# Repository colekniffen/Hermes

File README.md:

# Hermes

A small form factor, low power, RF module with a programmable STM32.  The goal of this project was to make a small board to mess around with RF and some basic DSP.

## Stack-up

I planned to manufacture this board through JLC PCB.  The service allows for cost-effective manufacturing with reasonable accuracy and constraints.  I decided to use an impedance-controlled, 4-layer stack-up because of the RF section (JLC04161H-7628).  This board is 1.6 mm thick with an outer copper weight of 1oz and inner copper weight of 0.5oz.  The stack-up information is important in determining the USB differential and RF antenna trace widths and/or spacing. 

## Design Considerations

### USB Connection
I decided to use a micro-USB connection for this board.  I chose this connector mainly for its size.  I did consider using USB-C since it's becoming more prevalent in modern electronics and similar in size.  However, USB-C has many connections which would not be useful in this case.  I did not need anything incredibly high-speed or with high power demand.  If one wanted to use USB-C with this board, it's possible to basically just swap out the connector and terminate it as per the USB-C specifications for USB-C to micro-USB.  If this is done, it may be wise to add current protection.  I left current protection out mainly to reduce the number of components, and the likelihood of micro-USB (due to the shape) having reverse current is incredibly low.  I did still include ESD protection though.

USB uses differential signals.  The specification for the USB protocol is to have 90 Ohm impedance traces.  To do this, I assumed a trace spacing of 8 mils.  The spacing could be reduced, but I chose this for ease of manufacturing.  Using the stack-up information and the differential spacing, trace widths are calculated to be 10.28 mil.

### Power
The USB connection to a host device will provide the board with 5V.  Most of the components on the board are designed for 3V3, so a voltage regulator is needed.  I chose the XC6206P332MR.  This is an efficient, low cost, and low noise LDO regulator. 

### Microcontroller
I chose to use the STM32L432KBU6 for this board.  It's low power and has a built in USB module.  This MCU doesn't have a ton of memory, but it will be used mainly for passing the RX/TX signal along to the host and do basic processing.  So, it has more than enough memory for its intended use.  Additionally, the core speed is more than enough to handle the transceiver's data.  

Assuming a 1ns rise time, which is faster than expected for this setup, the critical length is around 41.1 mm.  This means as long as the traces are less than 41.1 mm, impedance effects can largely be ignored for the MCU's digital signals (the board isn't even that long!).  Furthermore, assuming worst-case propagation delay, based on the PCB materials, of 180 ps/in, the slight differences in trace length won't make a huge difference.  The SPI traces are short and the fastest setup/hold times are around 1.5 ns, so the slight difference in SPI trace lengths (the skew in delay for the SPI signals is approximately 37.4 ps) will have virtually no effect on performance.  If the MCU was operating at GHz frequencies, problems would likely arise, but this length difference is okay for the fastest signals supported by this system. 

### Transceiver
I chose the nRF24L01+ which is a 2.4GHz transceiver (using [GFSK](https://en.wikipedia.org/wiki/Frequency-shift_keying#Gaussian_frequency-shift_keying) modulation).  This transceiver contains basically everything needed to perform the functions of most consumer electronics, so it is more than enough for experimenting with.  It has good documentation, a decent amount of customizability, and doesn't use a ton of power.  Additionally, The IC supports a variety of different antenna configurations, but I planned to connect a 2.4GHz passive, single-ended antenna.  Thus, I included the necessary matching and bias networks (assuming a 50 Ohm antenna) to meet the specifications as described by the data sheet.

To meet the impedance matching requirements, the antenna traces are to be 50 Ohms.  Using the stack-up information, the calculated trace width is 11.55mil.

## Datasheets
- [STM Datasheet](https://www.st.com/content/ccc/resource/technical/document/datasheet/24/01/9f/59/f0/83/47/fc/DM00257205.pdf/files/DM00257205.pdf/jcr:content/translations/en.DM00257205.pdf)
- [Transceiver Datasheet](https://www.sparkfun.com/datasheets/Components/SMD/nRF24L01Pluss_Preliminary_Product_Specification_v1_0.pdf)
- [ Linear and low-dropout regulator](https://www.mouser.com/datasheet/2/760/TOSL_S_A0007229533_1-2575067.pdf)

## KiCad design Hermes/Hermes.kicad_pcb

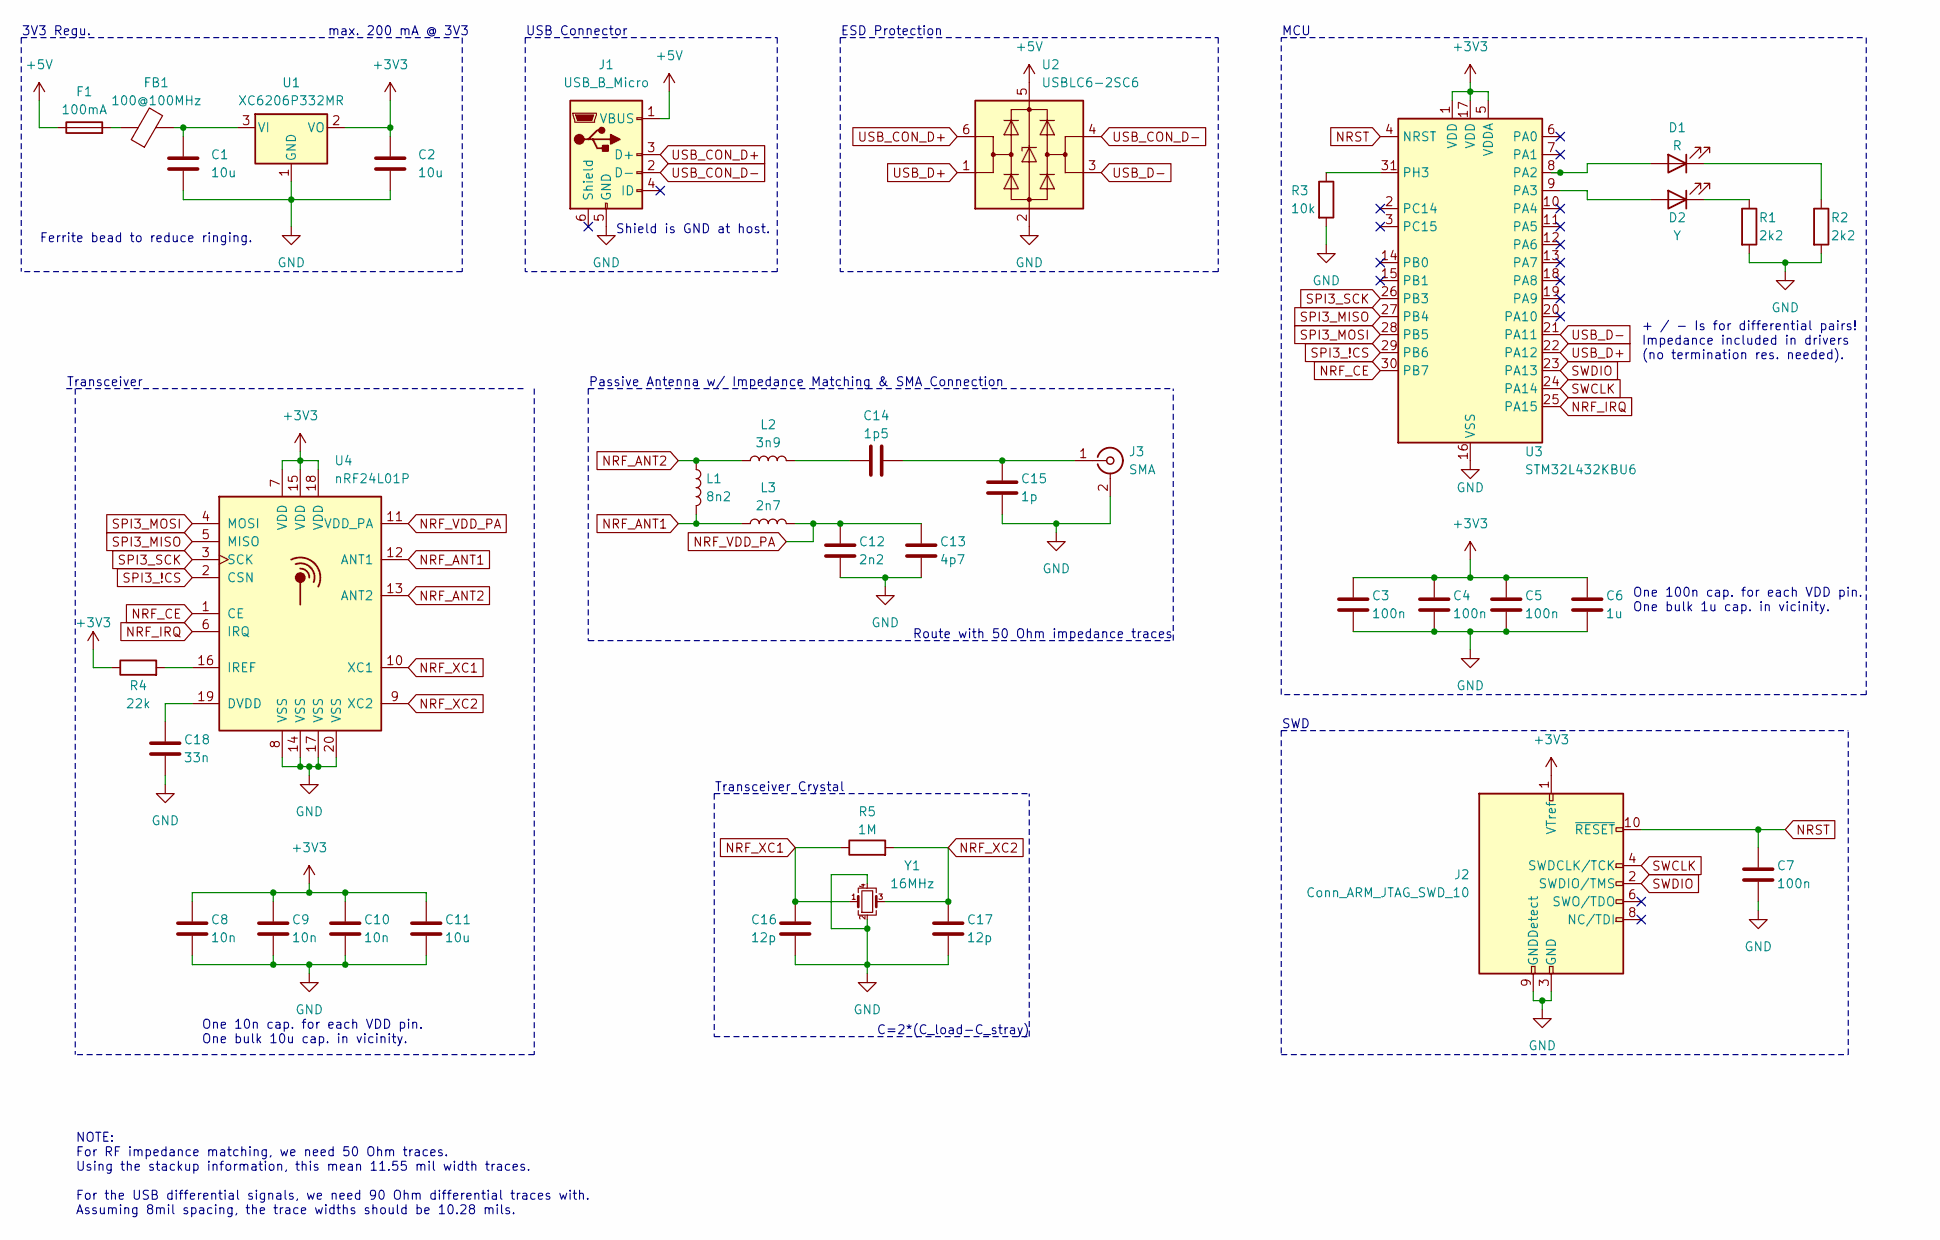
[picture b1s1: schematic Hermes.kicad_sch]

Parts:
C1, C2, C11: 10u; C_0603_1608Metric
C3, C4, C5, C7: 100n; C_0402_1005Metric
C6: 1u; C_0402_1005Metric
C8, C9, C10: 10n; C_0402_1005Metric
C12: 2n2; C_0402_1005Metric
C13: 4p7; C_0402_1005Metric
C14: 1p5; C_0402_1005Metric
C15: 1p; C_0402_1005Metric
C16, C17: 12p; C_0402_1005Metric
C18: 33n; C_0402_1005Metric
D1: R; LED_0603_1608Metric
D2: Y; LED_0603_1608Metric
F1: 100mA; Fuse_1206_3216Metric_Pad1.42x1.75mm_HandSolder
FB1: 100@100MHz; L_0805_2012Metric
J1: USB_B_Micro; USB_Micro-B_Molex-105017-0001
J2: Conn_ARM_JTAG_SWD_10; PinHeader_2x05_P1.27mm_Vertical
J3: SMA; SMA_Samtec_SMA-J-P-X-ST-EM1_EdgeMount
L1: 8n2; L_0402_1005Metric
L2: 3n9; L_0402_1005Metric
L3: 2n7; L_0402_1005Metric
R1, R2: 2k2; R_0603_1608Metric
R3: 10k; R_0402_1005Metric
R4: 22k; R_0402_1005Metric
R5: 1M; R_0402_1005Metric
U1: XC6206P332MR; SOT-23-3
U2: USBLC6-2SC6; SOT-23-6
U3: STM32L432KBU6; QFN-32-1EP_5x5mm_P0.5mm_EP3.45x3.45mm
U4: nRF24L01P; QFN-20-1EP_4x4mm_P0.5mm_EP2.5x2.5mm
Y1: 16MHz; Crystal_SMD_3225-4Pin_3.2x2.5mm

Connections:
+3V3: C2.1, C3.1, C4.1, C5.1, C6.1, C8.1, C9.1, C10.1, C11.1, J2.1 (VTref), R4.1, U1.2 (VO), U3.1 (VDD), U3.5 (VDDA), U3.17 (VDD), U4.7 (VDD), U4.15 (VDD), U4.18 (VDD)
+5V: F1.1, J1.1 (VBUS), U2.5 (VBUS)
GND: C1.2, C2.2, C3.2, C4.2, C5.2, C6.2, C7.2, C8.2, C9.2, C10.2, C11.2, C12.2, C13.2, C15.1, C16.2, C17.2, C18.2, J1.5 (GND), J2.3 (GND), J2.5 (GND), J2.9 (GNDDetect), J3.2 (Ext), R1.2, R2.2, R3.2, U1.1 (GND), U2.2 (GND), U3.16 (VSS), U3.32 (VSS), U3.33 (VSS), U4.8 (VSS), U4.14 (VSS), U4.17 (VSS), U4.20 (VSS), Y1.2, Y1.4
NRF_ANT1: L1.2, L3.1, U4.12 (ANT1)
NRF_ANT2: L1.1, L2.1, U4.13 (ANT2)
NRF_CE: U3.30 (PB7), U4.1 (CE)
NRF_IRQ: U3.25 (PA15), U4.6 (IRQ)
NRF_VDD_PA: C12.1, C13.1, L3.2, U4.11 (VDD_PA)
NRF_XC1: C16.1, R5.1, U4.10 (XC1), Y1.1
NRF_XC2: C17.1, R5.2, U4.9 (XC2), Y1.3
NRST: C7.1, J2.10 (~RESET), U3.4 (NRST)
unnamed: C14.1, L2.2
unnamed: D1.2 (A), U3.8 (PA2)
unnamed: D1.1 (K), R2.1
unnamed: D2.2 (A), U3.9 (PA3)
unnamed: D2.1 (K), R1.1
unnamed: F1.2, FB1.1
unnamed: C14.2, C15.2, J3.1 (In)
unnamed: C1.1, FB1.2, U1.3 (VI)
unnamed: R3.1, U3.31 (PH3)
unnamed: C18.1, U4.19 (DVDD)
unnamed: R4.2, U4.16 (IREF)
SPI3_!CS: U3.29 (PB6), U4.2 (CSN)
SPI3_MISO: U3.27 (PB4), U4.5 (MISO)
SPI3_MOSI: U3.28 (PB5), U4.4 (MOSI)
SPI3_SCK: U3.26 (PB3), U4.3 (SCK)
SWCLK: J2.4 (SWDCLK/TCK), U3.24 (PA14)
SWDIO: J2.2 (SWDIO/TMS), U3.23 (PA13)
USB_CON_D+: J1.3 (D+), U2.6 (I/O1)
USB_CON_D-: J1.2 (D-), U2.4 (I/O2)
USB_D+: U2.1 (I/O1), U3.22 (PA12)
USB_D-: U2.3 (I/O2), U3.21 (PA11)

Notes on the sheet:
Transceiver Crystal
NOTE: For RF impedance matching, we need 50 Ohm traces. Using the stackup information, this mean 11.55 mil width traces. For the USB differential signals, we need 90 Ohm differential traces with. Assuming 8mil spacing, the trace widths should be 10.28 mils.
C=2*(C_load-C_stray)
One 100n cap. for each VDD pin. One bulk 1u cap. in vicinity.
USB Connector
Shield is GND at host.
max. 200 mA @ 3V3
Passive Antenna w/ Impedance Matching & SMA Connection
Route with 50 Ohm impedance traces
Ferrite bead to reduce ringing.
Transceiver
SWD
One 10n cap. for each VDD pin. One bulk 10u cap. in vicinity.
MCU
+ / - Is for differential pairs! Impedance included in drivers (no termination res. needed).
ESD Protection
3V3 Regu.

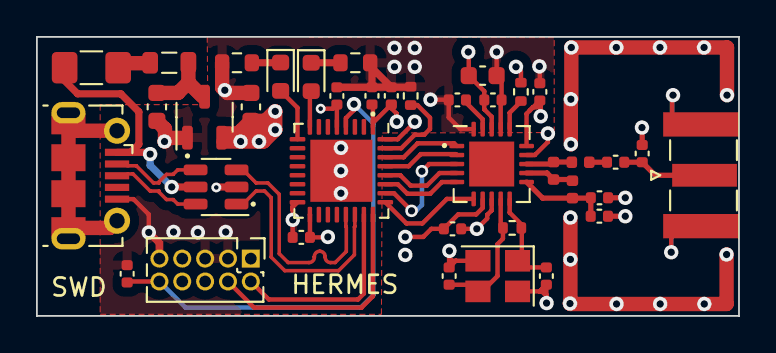
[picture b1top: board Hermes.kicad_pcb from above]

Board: 4 copper layers, 39.0 x 15.5 mm, 38 parts (0 on the bottom side), 32 nets.

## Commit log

2023-08-25 Board and schematic
2023-08-25 Cleanup files and comments
2023-08-25 Documentation
2023-08-25 Fix image
2023-08-25 Final edits
2023-08-25 Updating schematic comments
2023-08-25 Add layout to readme
2023-08-26 Update schematic image in readme
2023-08-26 Fix v2 for readme
2023-08-28 Update README.md with critical length discussion
2023-08-28 Update README.md to fix wording
2023-08-28 Update README.md for grammer fixes
2023-08-28 Update README.md to explain delay check
2023-08-28 Final edit of README :)
2023-08-29 Again, I'm bad at grammar. Whoops
